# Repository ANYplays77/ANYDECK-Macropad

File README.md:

# ANYDECK Macropad

ANYDECK is a 6-key mechanical macropad I designed to be simple and useful. It uses a XIAO RP2040 controller and features two rotary encoders, a small OLED screen, and RGB lighting.

The goal was to make a sturdy desktop tool that is easy to build for managing shortcuts or volume.

---

## Project Overview
This is a photo of the finished macropad inside its 3D printed case.

---

## Schematic
The build uses a XIAO RP2040. The keys are wired with diodes to prevent signal conflicts. 

---

## PCB
The printed circuit board is a compact double-layer design that holds all parts,

---

## Case and Assembly
The case is designed in two parts. The switches click into the top plate before being soldered to the PCB to keep everything solid.

**Top case view:**

**Internal assembly:**

---

## Bill of Materials (BOM)

* 1x Seeed Studio XIAO RP2040
* 6x Mechanical switches (MX compatible)
* 2x EC11 rotary encoders
* 1x SSD1306 OLED screen (I2C)
* 8x 1N4148 Diodes
* 2x SK6812 RGB LEDs
* 1x 3D printed case (Top and Base)

---

## Build Instructions

1. Solder the diodes to the PCB. Make sure the black line on the diode matches the mark on the board.
2. Solder the XIAO RP2040 and the two RGB LEDs.
3. Install and solder the OLED screen and the two rotary encoders.
4. Put the switches into the top case, place the PCB over them, and solder the switch pins.
5. Close the case with the bottom plate and add your keycaps and encoder knobs.

---

## How to Use

Once you plug it in via USB-C, your computer will see ANYDECK as a keyboard. You can change shortcuts by opening the code.py file on the USB drive (using CircuitPython/KMK). The encoders control volume and scrolling by default, and the screen shows your current navigation info.

## RESULT

## video of the assembly
https://www.instagram.com/reel/DYsDTL5I2ws/?igsh=YTVxaW56M2NmeHox ‎ ‎

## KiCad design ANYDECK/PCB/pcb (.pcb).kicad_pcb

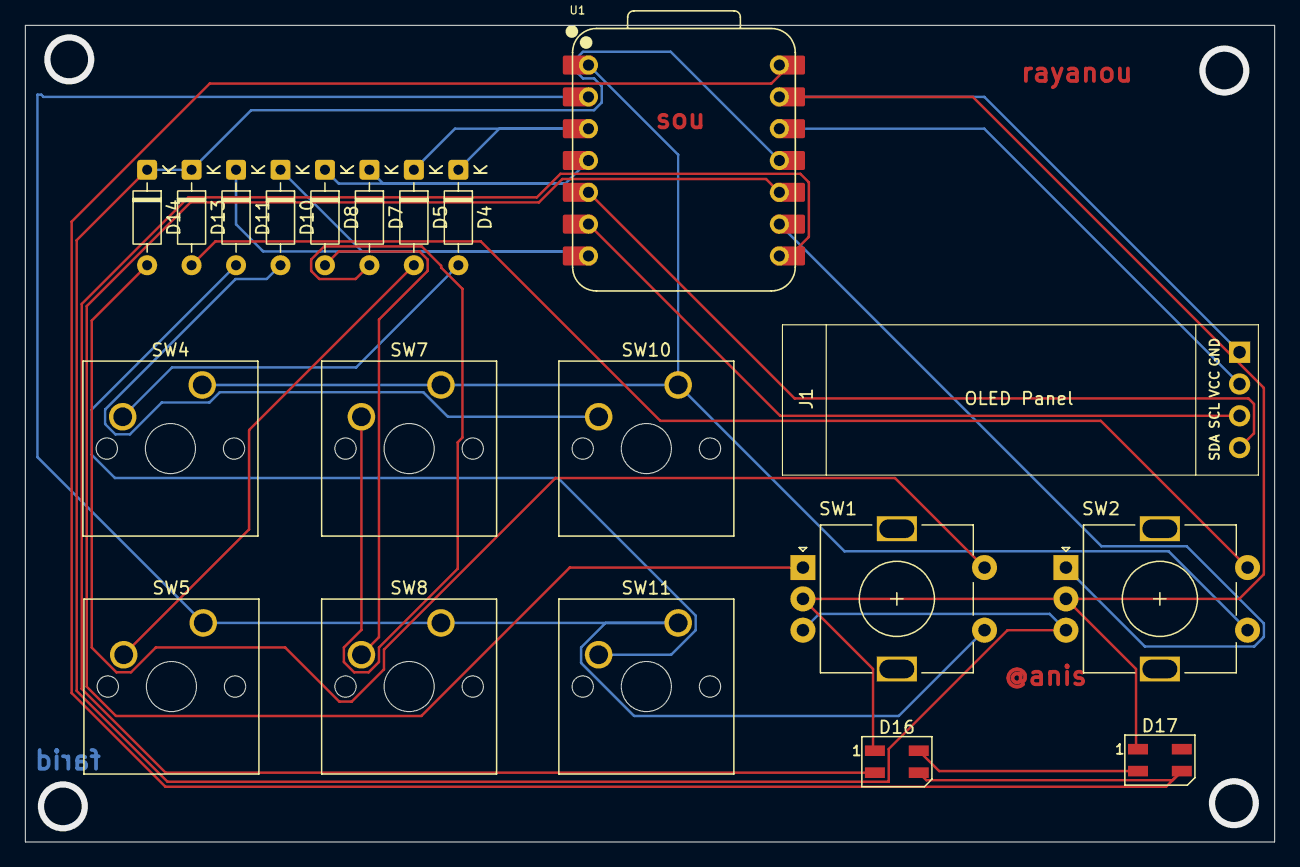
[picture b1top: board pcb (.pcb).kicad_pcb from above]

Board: 2 copper layers, 99.7 x 65.2 mm, 20 parts (0 on the bottom side), 23 nets.

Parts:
D4, D5, D7, D8, D10, D11, D13, D14: 1N4148; D_DO-35_SOD27_P7.62mm_Horizontal
D16, D17: SK6812; LED_SK6812MINI_PLCC4_3.5x3.5mm_P1.75mm
J1: ssd 1306; SSD1306-0.91-OLED-4pin-128x32
SW1, SW2: RotaryEncoder_Switch; RotaryEncoder_Alps_EC11E-Switch_Vertical_H20mm
SW4, SW5, SW7, SW8, SW10, SW11: SW_Push; SW_Cherry_MX_1.00u_PCB
U1: XIAO-RP2040-DIP

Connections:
unnamed: D4.2 (A), SW4.2
unnamed: D4.1 (K), D5.1 (K), U1.3 (GPIO28/ADC2/A2)
unnamed: D5.2 (A), SW5.2
unnamed: D7.2 (A), SW7.2
unnamed: D7.1 (K), D8.1 (K), U1.4 (GPIO29/ADC3/A3)
unnamed: D8.2 (A), SW8.2
unnamed: D10.2 (A), SW10.2
unnamed: D10.1 (K), D11.1 (K), U1.7 (GPIO0/TX)
unnamed: D11.2 (A), SW11.2
unnamed: D13.2 (A), SW2.S2
unnamed: D13.1 (K), D14.1 (K), SW1.B, SW2.B, U1.11 (GPIO3/MOSI)
unnamed: D14.2 (A), SW1.S2
unnamed: D16.2 (DIN), U1.8 (GPIO1/RX)
unnamed: D16.4 (DOUT), D17.2 (DIN)
unnamed: D16.3 (VDD), D17.3 (VDD), U1.14 (VBUS)
unnamed: D16.1 (VSS), D17.1 (VSS), J1.1, SW1.C, SW2.C, U1.13 (GND)
unnamed: J1.2, U1.12 (3V3)
unnamed: J1.3, U1.6 (GPIO7/SCL)
unnamed: J1.4, U1.5 (GPIO6/SDA)
unnamed: SW2.A, U1.9 (GPIO2/SCK)
unnamed: SW1.A, U1.10 (GPIO4/MISO)
unnamed: SW2.S1, SW4.1, SW7.1, SW10.1, U1.1 (GPIO26/ADC0/A0)
unnamed: SW1.S1, SW5.1, SW8.1, SW11.1, U1.2 (GPIO27/ADC1/A1)

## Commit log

2026-02-26 Create Pic
2026-06-08 Rename nnn.png to nnn.PNG
